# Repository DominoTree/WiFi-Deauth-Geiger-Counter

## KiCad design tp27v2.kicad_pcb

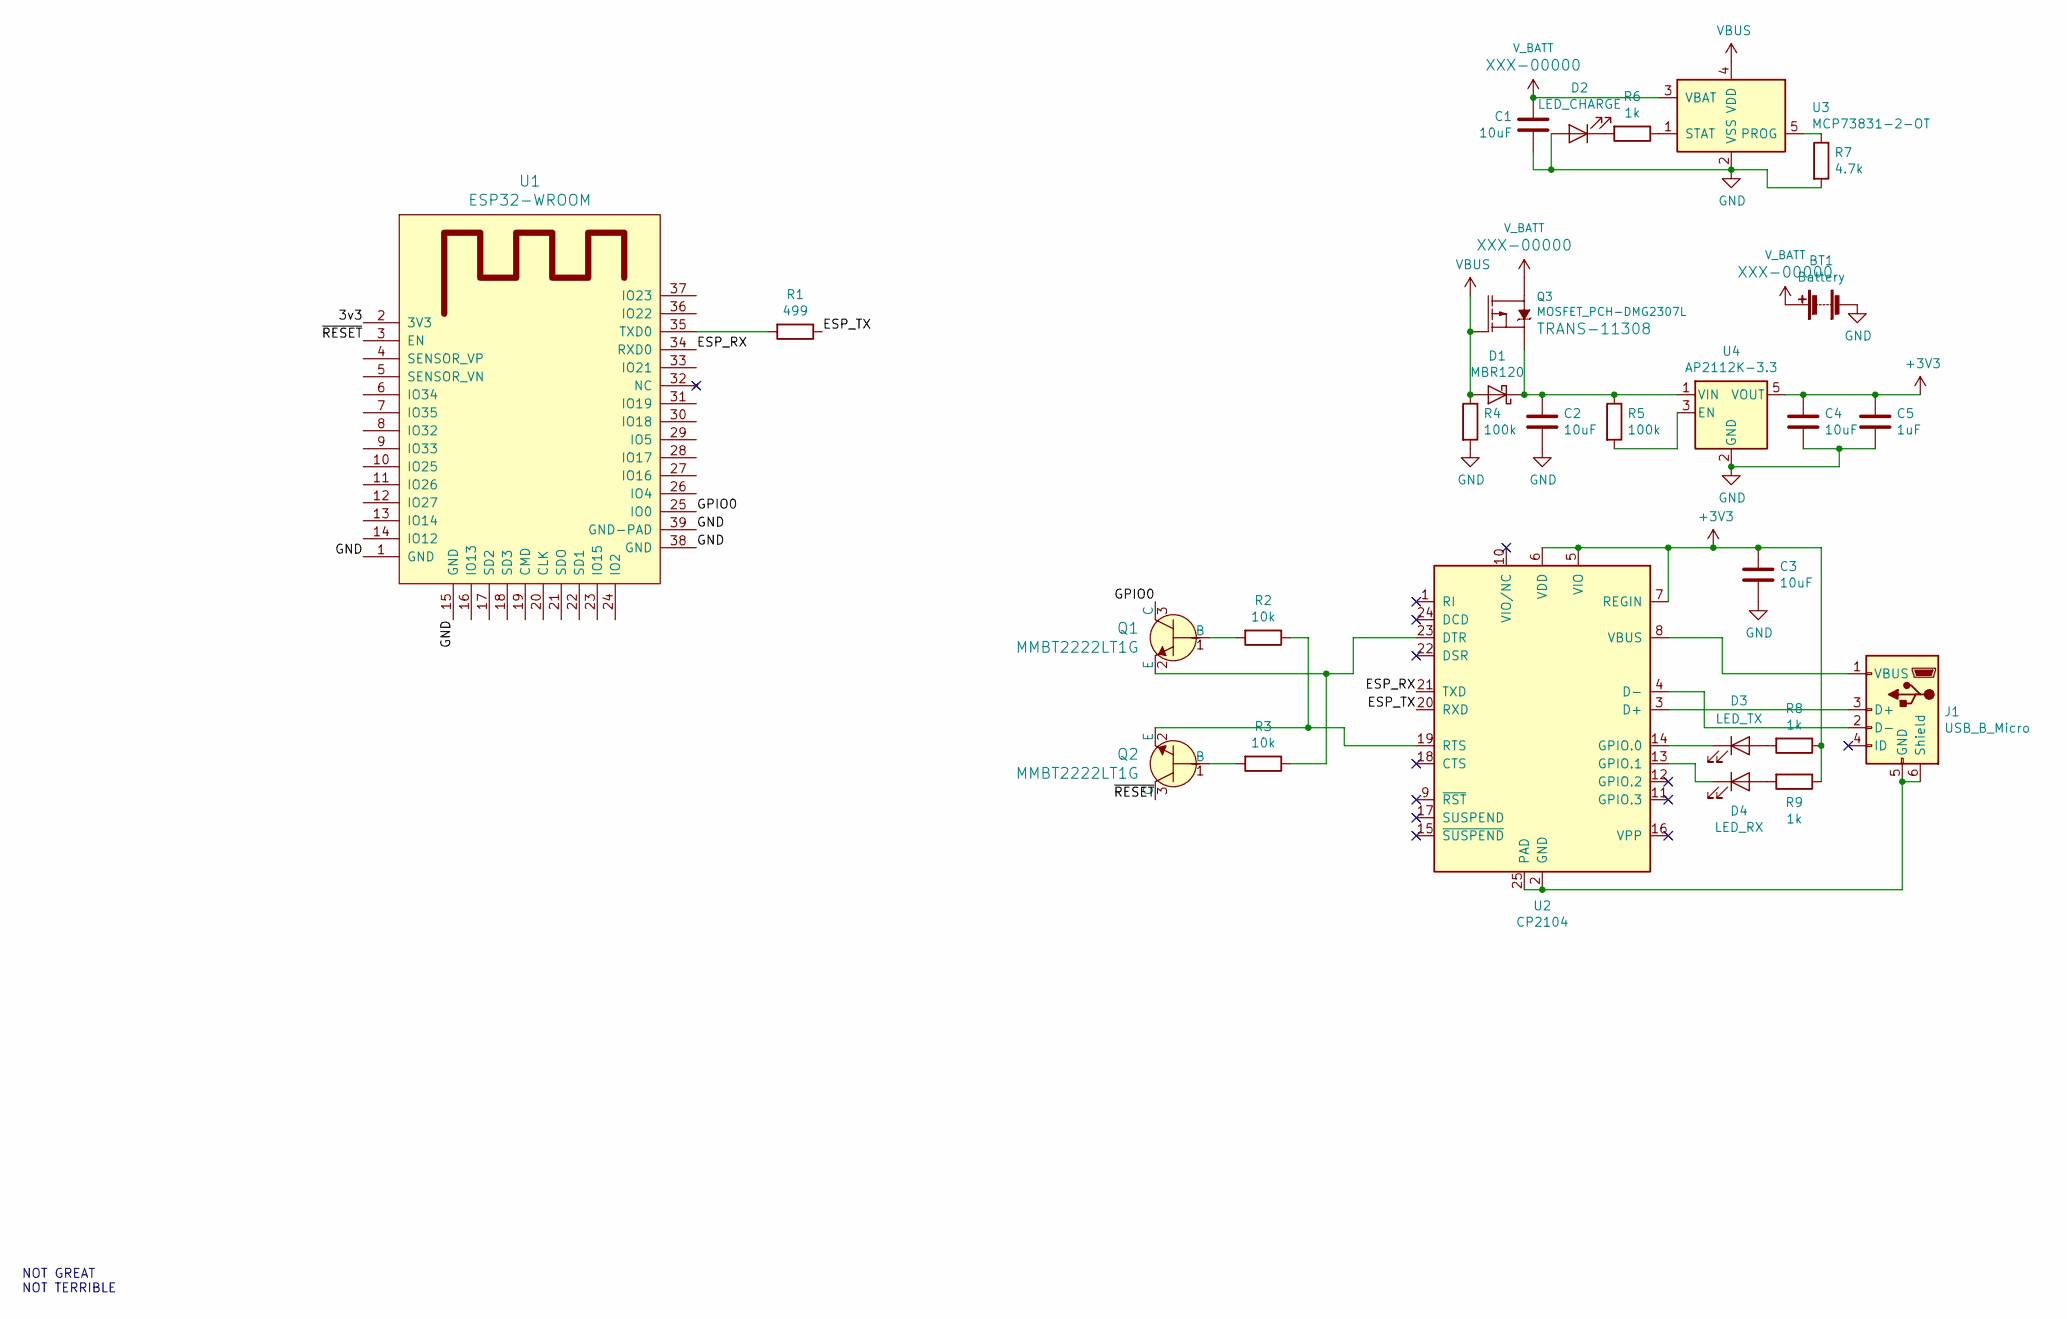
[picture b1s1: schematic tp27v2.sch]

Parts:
BT1: Battery; BatteryHolder_MPD_BH-18650-PC2
C1, C2, C3, C4: 10uF; C_1206_3216Metric
C5: 1uF; C_1206_3216Metric
D1: MBR120; D_1206_3216Metric
D2: LED_CHARGE; LED_1206_3216Metric
D3: LED_TX; LED_1206_3216Metric
D4: LED_RX; LED_1206_3216Metric
J1: USB_B_Micro; USB_Micro-B_Molex_47346-0001
Q1, Q2: MMBT2222LT1G; SOT-23; MPN MMBT2222LT1G; Digi-Key_PN MMBT2222LT1GOSCT-ND
Q3: MOSFET_PCH-DMG2307L; SOT-23
R1: 499; R_1206_3216Metric
R2, R3: 10k; R_1206_3216Metric
R4, R5: 100k; R_1206_3216Metric
R6, R8, R9: 1k; R_1206_3216Metric
R7: 4.7k; R_1206_3216Metric
U1: ESP32-WROOM; ESP32-WROOM-32
U2: CP2104; QFN-24-1EP_4x4mm_P0.5mm_EP2.6x2.6mm
U3: MCP73831-2-OT; SOT-23-5
U4: AP2112K-3.3; SOT-23-5

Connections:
+3V3: C3.1, C4.1, C5.1, R8.1, R9.1, U2.5 (VIO), U2.6 (VDD), U2.7 (REGIN), U4.5 (VOUT)
/ESP_RX: U1.34 (RXD0), U2.21 (TXD)
/ESP_TX: R1.1, U2.20 (RXD)
/GPIO0: Q1.3 (C), U1.25 (IO0)
/~RESET: Q2.3 (C), U1.3 (EN)
GND: BT1.2 (-), C1.1, C2.2, C3.2, C4.2, C5.2, D2.2 (A), R4.2, R7.2, U1.1 (GND), U1.15 (GND), U1.38 (GND), U1.39 (GND-PAD), U3.2 (VSS), U4.2 (GND)
unnamed: C2.1, D1.1 (K), Q3.2 (S), R5.1, U4.1 (VIN)
unnamed: D2.1 (K), R6.2
unnamed: D3.1 (K), U2.14 (GPIO.0)
unnamed: D3.2 (A), R8.2
unnamed: D4.1 (K), U2.13 (GPIO.1)
unnamed: D4.2 (A), R9.2
unnamed: J1.1 (VBUS), U2.8 (VBUS)
unnamed: J1.2 (D-), U2.4 (D-)
unnamed: J1.3 (D+), U2.3 (D+)
unnamed: J1.5 (GND), J1.6 (Shield), U2.2 (GND), U2.25 (PAD)
unnamed: Q1.1 (B), R2.2
unnamed: Q1.2 (E), R3.1, U2.23 (DTR)
unnamed: Q2.1 (B), R3.2
unnamed: Q2.2 (E), R2.1, U2.19 (RTS)
unnamed: R1.2, U1.35 (TXD0)
unnamed: R5.2, U4.3 (EN)
unnamed: R6.1, U3.1 (STAT)
unnamed: R7.1, U3.5 (PROG)
VBUS: D1.2 (A), Q3.1 (G), R4.1, U3.4 (VDD)
V_BATT: BT1.1 (+), C1.2, Q3.3 (D), U3.3 (VBAT)

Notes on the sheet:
NOT GREAT NOT TERRIBLE

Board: 2 copper layers, 27 parts (1 on the bottom side), 26 nets, no tracks yet.

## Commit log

2020-10-06 move
